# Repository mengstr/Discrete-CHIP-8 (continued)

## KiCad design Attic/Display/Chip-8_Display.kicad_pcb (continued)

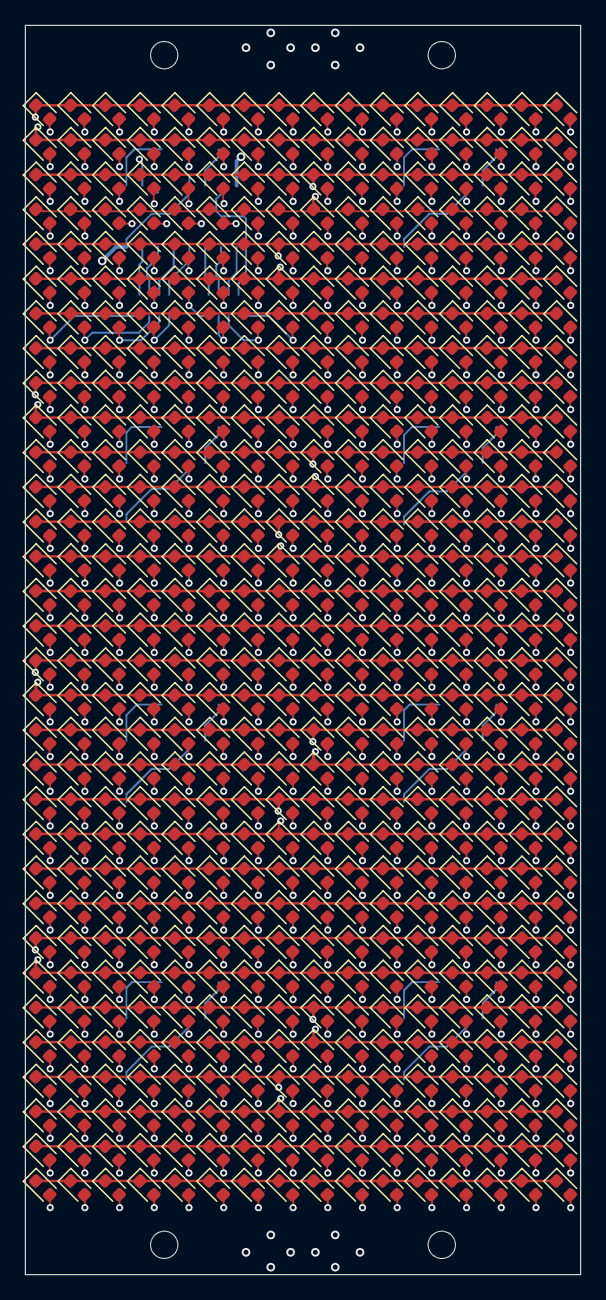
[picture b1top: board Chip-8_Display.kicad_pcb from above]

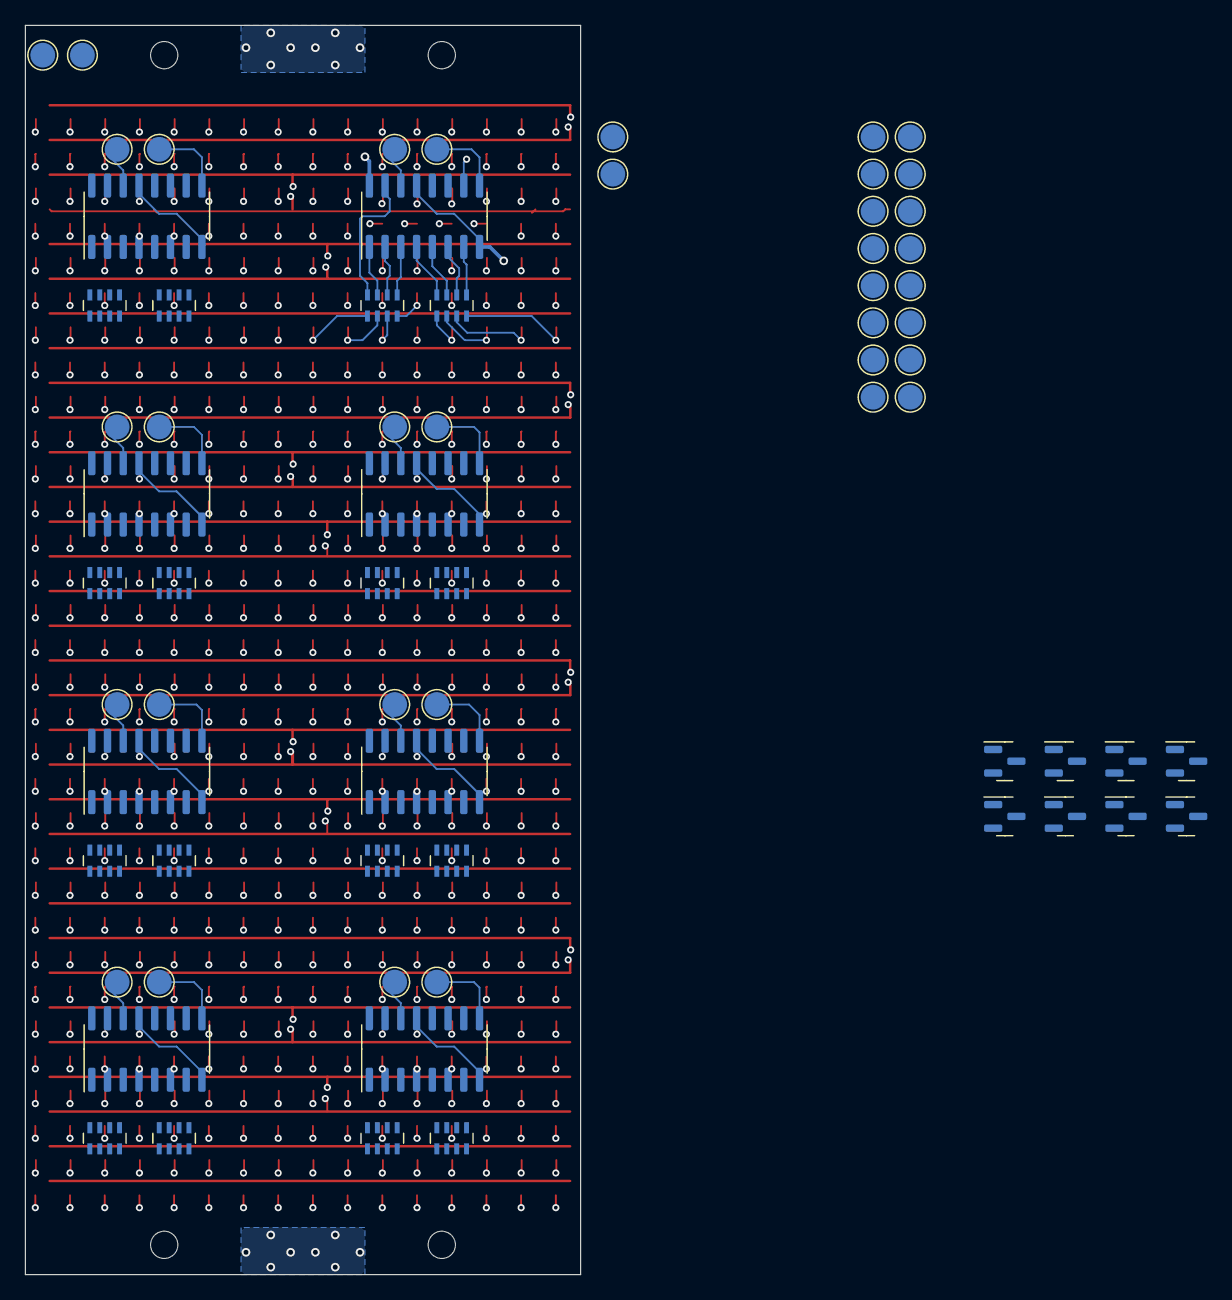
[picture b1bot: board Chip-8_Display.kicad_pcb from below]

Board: 4 copper layers, 44.8 x 100.8 mm, 584 parts (68 on the bottom side), 164 nets.

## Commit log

2023-08-20 Igonre lockfiles
2023-08-20 Ignore production files
2023-08-20 WIP 95% finshed
2023-08-21 WIP 99.99% routing done
2023-08-21 100% Routed.
2023-08-21 Finished
